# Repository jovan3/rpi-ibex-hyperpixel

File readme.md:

# RPi Ibex (Hyperpixel edition)

RPi Ibex is a Raspberry Pi Zero based portable computer. The goal of the project is to provide a way to use Raspberry Pi Zero as a portable computer using parts that are available, cheap and relatively easy to solder (no exotic keyboard controller chips required). 

This repository contains Kicad project files for the PCB. The keyboard is just simple push buttons soldered directly on the board. The keyboard controller is an Atmega 328P.

## Board renderings

Kicad 3D renderings of the front and back of the PCB:

Front:

Back:

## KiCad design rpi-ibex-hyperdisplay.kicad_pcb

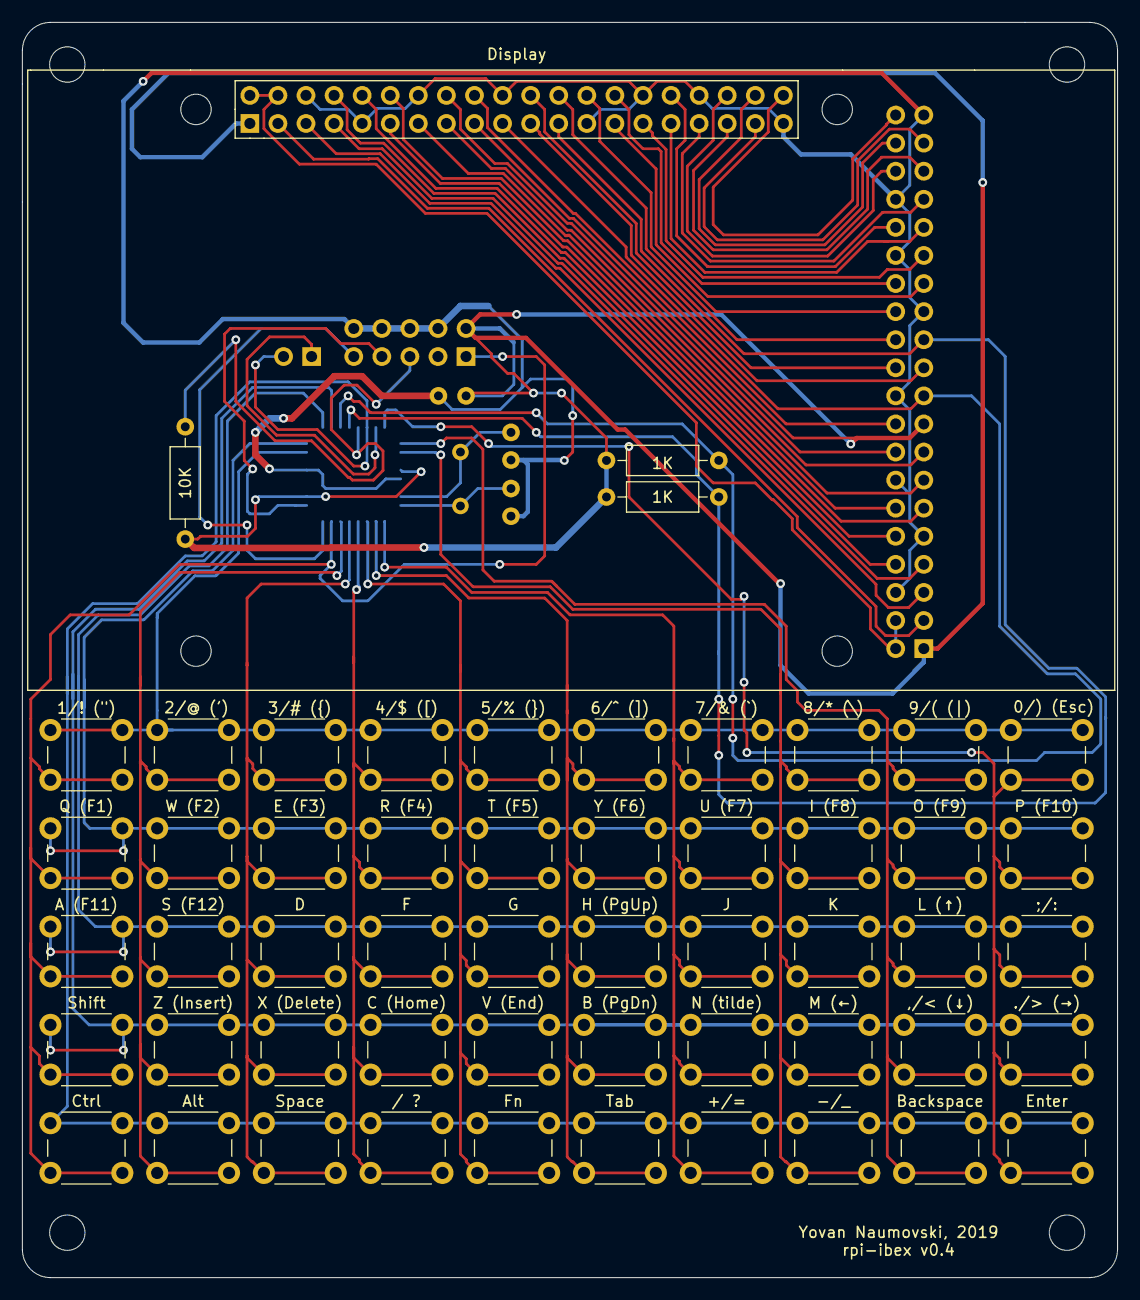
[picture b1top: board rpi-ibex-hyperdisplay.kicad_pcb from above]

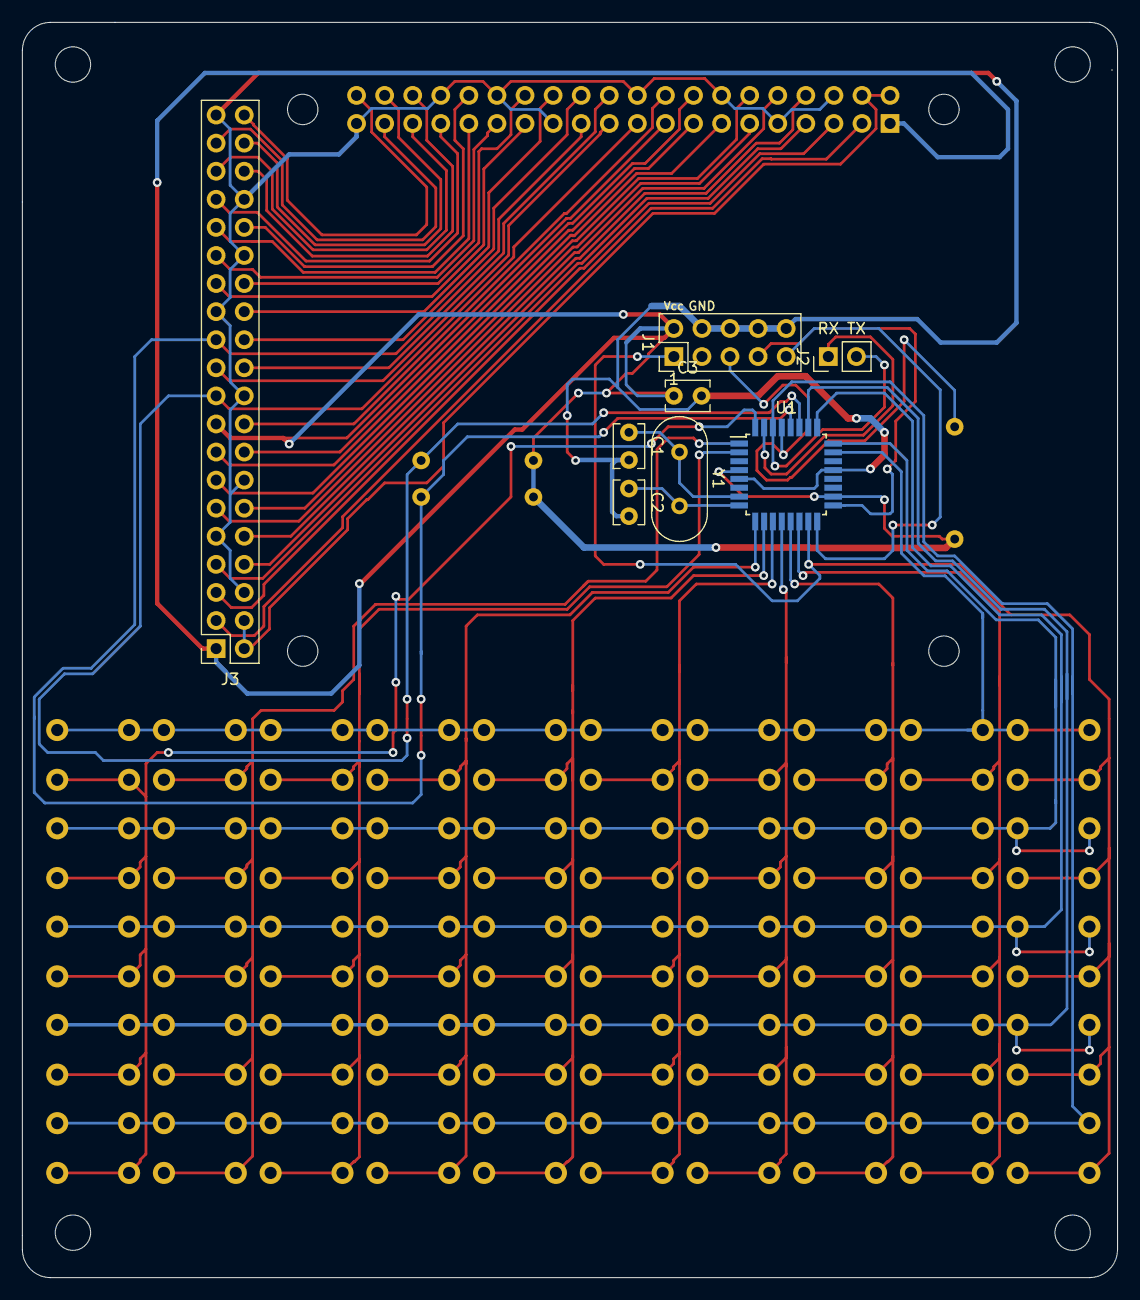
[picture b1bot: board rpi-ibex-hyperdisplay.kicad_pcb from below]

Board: 2 copper layers, 99.1 x 113.5 mm, 62 parts (8 on the bottom side), 52 nets.

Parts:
0/) (Esc), 1/! ("), 2/@ ('), 3/# ({), 4/$ ([), 5/% (}), 6/^ (]), 7/& (`), 8/* (\), 9/( (|), ./> (→): SW_Push; SW_PUSH_6mm_H5mm
1K, 1K#2: 1K; R_Axial_DIN0207_L6.3mm_D2.5mm_P10.16mm_Horizontal
10K: 10K; R_Axial_DIN0207_L6.3mm_D2.5mm_P10.16mm_Horizontal
+/=: SW_Push; SW_PUSH_6mm_H5mm
,/< (↓): SW_Push; SW_PUSH_6mm_H5mm
-/_: SW_Push; SW_PUSH_6mm_H5mm
/ ?: SW_Push; SW_PUSH_6mm_H5mm
;/:: SW_Push; SW_PUSH_6mm_H5mm
A (F11): SW_Push; SW_PUSH_6mm_H5mm
Alt: SW_Push; SW_PUSH_6mm_H5mm
B (PgDn): SW_Push; SW_PUSH_6mm_H5mm
Backspace: SW_Push; SW_PUSH_6mm_H5mm
C1, C2: 22pF; C_Disc_D3.8mm_W2.6mm_P2.50mm
C3: 100nF; C_Disc_D3.8mm_W2.6mm_P2.50mm
C (Home): SW_Push; SW_PUSH_6mm_H5mm
Ctrl: SW_Push; SW_PUSH_6mm_H5mm
D: SW_Push; SW_PUSH_6mm_H5mm
Display: Hyperpixel_4.0_Touch
E (F3): SW_Push; SW_PUSH_6mm_H5mm
Enter: SW_Push; SW_PUSH_6mm_H5mm
F: SW_Push; SW_PUSH_6mm_H5mm
Fn: SW_Push; SW_PUSH_6mm_H5mm
G: SW_Push; SW_PUSH_6mm_H5mm
H (PgUp): SW_Push; SW_PUSH_6mm_H5mm
I (F8): SW_Push; SW_PUSH_6mm_H5mm
J: SW_Push; SW_PUSH_6mm_H5mm
J1: Conn_02x05_Odd_Even; PinHeader_2x05_P2.54mm_Vertical
J2: USART_Connector_1; PinHeader_1x02_P2.54mm_Vertical
J3: Raspberry_Pi_2_3; PinSocket_2x20_P2.54mm_Vertical
K: SW_Push; SW_PUSH_6mm_H5mm
L (↑): SW_Push; SW_PUSH_6mm_H5mm
M (←): SW_Push; SW_PUSH_6mm_H5mm
N (tilde): SW_Push; SW_PUSH_6mm_H5mm
O (F9): SW_Push; SW_PUSH_6mm_H5mm
P (F10): SW_Push; SW_PUSH_6mm_H5mm
Q (F1): SW_Push; SW_PUSH_6mm_H5mm
R (F4): SW_Push; SW_PUSH_6mm_H5mm
S (F12): SW_Push; SW_PUSH_6mm_H5mm
Shift: SW_Push; SW_PUSH_6mm_H5mm
Space: SW_Push; SW_PUSH_6mm_H5mm
T (F5): SW_Push; SW_PUSH_6mm_H5mm
Tab: SW_Push; SW_PUSH_6mm_H5mm
U1: ATmega328PB-AU; TQFP-32_7x7mm_P0.8mm
U (F7): SW_Push; SW_PUSH_6mm_H5mm
V (End): SW_Push; SW_PUSH_6mm_H5mm
W (F2): SW_Push; SW_PUSH_6mm_H5mm
X (Delete): SW_Push; SW_PUSH_6mm_H5mm
Y1: 16MHz; Crystal_HC49-U_Vertical
Y (F6): SW_Push; SW_PUSH_6mm_H5mm
Z (Insert): SW_Push; SW_PUSH_6mm_H5mm

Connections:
5V: Display.2, Display.4, J3.2, J3.4
BCM0: Display.27, J3.27
BCM1: Display.28, J3.28
BCM2: Display.3, J3.3
BCM3: Display.5, J3.5
BCM4: Display.7, J3.7
BCM5: Display.29, J3.29
BCM6: Display.31, J3.31
BCM7: Display.26, J3.26
BCM8: Display.24, J3.24
BCM9: Display.21, J3.21
BCM10: 1K.1, Display.19, J3.19, U1.27
BCM11: 1K#2.1, Display.23, J3.23, U1.28
BCM12: Display.32, J3.32
BCM13: Display.33, J3.33
BCM14: Display.8, J3.8
BCM15: Display.10, J3.10
BCM16: Display.36, J3.36
BCM17: Display.11, J3.11
BCM18: Display.12, J3.12
BCM19: Display.35, J3.35
BCM20: Display.38, J3.38
BCM21: Display.40, J3.40
BCM22: Display.15, J3.15
BCM23: Display.16, J3.16
BCM24: Display.18, J3.18
BCM25: Display.22, J3.22
BCM26: Display.37, J3.37
BCM27: Display.13, J3.13
GND: C1.2, C2.2, C3.2, Display.6, Display.9, Display.14, Display.20, Display.25, Display.30, Display.34, Display.39, J1.4, J1.6, J1.8, J1.10, J3.6, J3.9, J3.14, J3.20, J3.25, J3.30, J3.34, J3.39, U1.5, U1.21
KB_COL_1: 1/! (").2, A (F11).2, Ctrl.2, J1.1, Q (F1).2, Shift.2, U1.15
KB_COL_2: 2/@ (').2, Alt.2, S (F12).2, U1.14, W (F2).2, Z (Insert).2
KB_COL_3: 3/# ({).2, D.2, E (F3).2, Space.2, U1.13, X (Delete).2
KB_COL_4: 4/$ ([).2, / ?.2, C (Home).2, F.2, R (F4).2, U1.12
KB_COL_5: 5/% (}).2, Fn.2, G.2, T (F5).2, U1.11, V (End).2
KB_COL_6: 6/^ (]).2, B (PgDn).2, H (PgUp).2, Tab.2, U1.10, Y (F6).2
KB_COL_7: 7/& (`).2, +/=.2, J.2, N (tilde).2, U1.9, U (F7).2
KB_COL_8: 8/* (\).2, -/_.2, I (F8).2, K.2, M (←).2, U1.2
KB_COL_9: 9/( (|).2, ,/< (↓).2, Backspace.2, L (↑).2, O (F9).2, U1.1
KB_COL_10: 0/) (Esc).2, ./> (→).2, ;/:.2, Enter.2, P (F10).2, U1.32
KB_ROW_1: 0/) (Esc).1, 1/! (").1, 2/@ (').1, 3/# ({).1, 4/$ ([).1, 5/% (}).1, 6/^ (]).1, 7/& (`).1, 8/* (\).1, 9/( (|).1, U1.23
KB_ROW_2: E (F3).1, I (F8).1, O (F9).1, P (F10).1, Q (F1).1, R (F4).1, T (F5).1, U1.24, U (F7).1, W (F2).1, Y (F6).1
KB_ROW_3: ;/:.1, A (F11).1, D.1, F.1, G.1, H (PgUp).1, J.1, K.1, L (↑).1, S (F12).1, U1.25
KB_ROW_4: ,/< (↓).1, ./> (→).1, B (PgDn).1, C (Home).1, M (←).1, N (tilde).1, Shift.1, U1.26, V (End).1, X (Delete).1, Z (Insert).1
KB_ROW_5: +/=.1, -/_.1, / ?.1, Alt.1, Backspace.1, Ctrl.1, Enter.1, Fn.1, J2.2, Space.1, Tab.1, U1.30
MISO: J1.9, U1.16
unnamed: J2.1, U1.31
RESET: 10K.1, J1.5, U1.29
RPI_3.3V: 1K.2, 1K#2.2, 10K.2, C3.1, Display.1, Display.17, J1.2, J3.1, J3.17, U1.4, U1.18
SCK: J1.7, U1.17
XTAL1: C1.1, U1.7, Y1.1
XTAL2: C2.1, U1.8, Y1.2

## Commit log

2019-09-10 change v0.2 to be designed around the Hyperpixel 4.0 touch screen
2019-10-02 mirror flip the hyperpixel connector (oops :/)
2019-10-02 move hyperpixel footprint silkscreen and other layers from back to front
2019-10-03 rotate the rpi pin headers so that its usb ports are facing outwards the board
2019-10-04 better route tracks layout for the connection between the raspberry pi and hyperpixel display
2019-10-04 improve layout
2021-12-13 add pcb images
2021-12-13 add readme
2021-12-13 Create LICENSE
